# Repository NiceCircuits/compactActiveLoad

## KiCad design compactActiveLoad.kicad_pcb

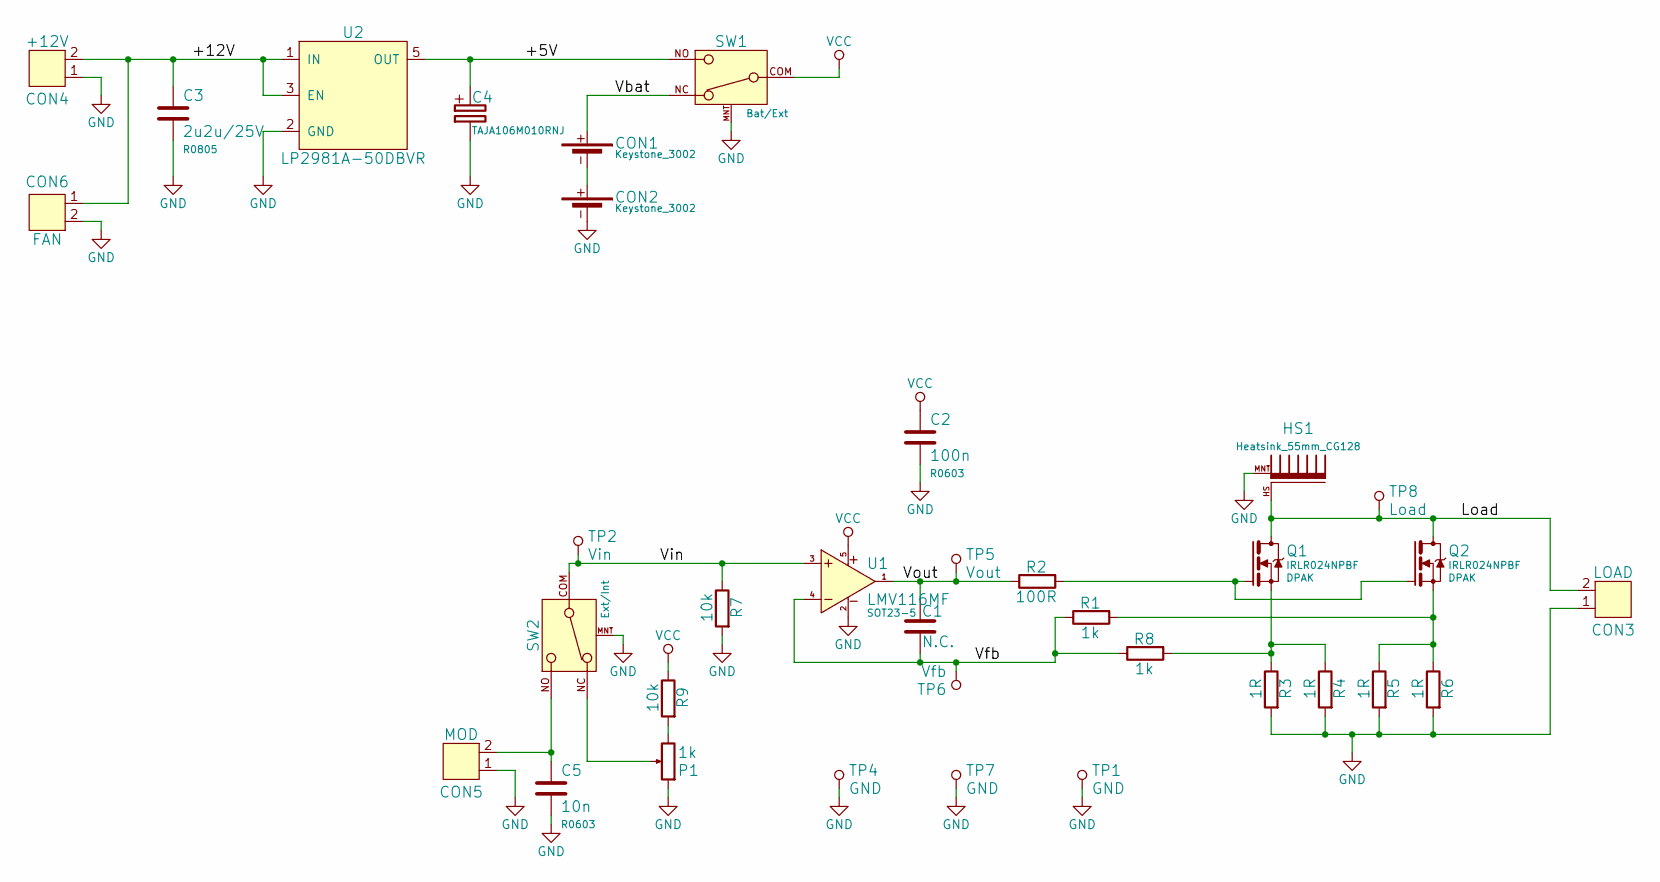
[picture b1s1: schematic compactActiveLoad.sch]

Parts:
C1: N.C.; R0603
C2: 100n; R0603
C3: 2u2u/25V; R0805
C4: TAJA106M010RNJ; TANTAL_A
C5: 10n; R0603
CON1, CON2: Keystone_3002
CON3: LOAD; PIN1x2ANGLE_SMD
CON4: +12V; PIN1x2ANGLE_SMD
CON5: MOD; PIN1x2ANGLE_SMD
CON6: FAN; PAD2_2x3
HS1: Heatsink_55mm_CG128
P1: 1k; pot_ACP_CA6VSMD+6001
Q1, Q2: IRLR024NPBF; DPAK
R1, R8: 1k; R0603
R2: 100R; R0603
R3, R4, R5, R6: 1R; R2010
R7, R9: 10k; R0603
SW1: Bat/Ext; SW_1290F1123
SW2: Ext/Int; SW_1290F1123
TP1, TP4, TP7: GND; TP_1mm
TP2: Vin; TP_1mm
TP5: Vout; TP_1mm
TP6: Vfb; TP_1mm
TP8: Load; TP_1mm
U1: LMV116MF; SOT23-5
U2: LP2981A-50DBVR; SOT23-5

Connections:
/+5V: C4.1, SW1.NO, U2.5 (OUT)
/+12V: C3.1, CON4.2, CON6.1, U2.1 (IN), U2.3 (EN)
/Load: CON3.2, HS1.HS, Q1.4 (D), Q2.4 (D), TP8.1
/Vbat: CON1.+, SW1.NC
/Vfb: C1.2, R1.2, R8.2, TP6.1, U1.4 (-)
/Vin: R7.2, SW2.COM, TP2.1, U1.3 (+)
/Vout: C1.1, R2.2, TP5.1, U1.1 (OUT)
GND: C2.2, C3.2, C4.2, C5.2, CON2.-, CON3.1, CON4.1, CON5.1, CON6.2, HS1.MNT, P1.1, R3.1, R4.1, R5.1, R6.1, R7.1, SW1.MNT, SW2.MNT, TP1.1, TP4.1, TP7.1, U1.2 (VSS), U2.2 (GND)
unnamed: C5.1, CON5.2, SW2.NO
unnamed: CON1.-, CON2.+
unnamed: P1.2, SW2.NC
unnamed: P1.3, R9.1
unnamed: Q1.1 (G), Q2.1 (G), R2.1
unnamed: Q1.3 (S), R3.2, R4.2, R8.1
unnamed: Q2.3 (S), R1.1, R5.2, R6.2
VCC: C2.1, R9.2, SW1.COM, U1.5 (VDD)

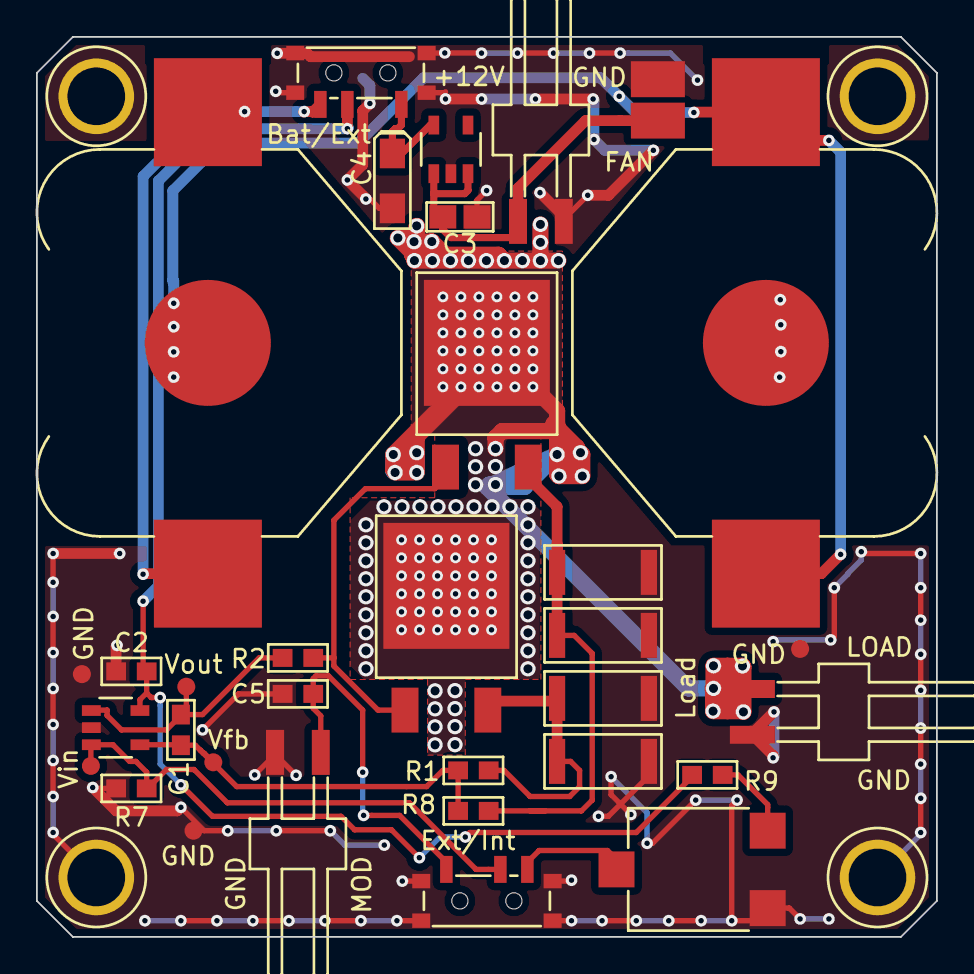
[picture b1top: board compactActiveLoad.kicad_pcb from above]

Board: 2 copper layers, 50.0 x 50.0 mm, 40 parts (1 on the bottom side), 16 nets.

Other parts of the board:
MECH1, MECH2, MECH3, MECH4: FIX-3-5
MECH5: compactActiveLoad_BottomCover

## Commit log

2015-06-15 Add key components. Rough placement.
2015-06-19 Placement
2015-06-19 routing
2015-06-22 Routed
2015-06-22 Little more thermal vias
2015-12-20 Some changes
